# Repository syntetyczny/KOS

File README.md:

KOS
===

Another RepRap controller based on teensylu/printrboard and more. 

Project and all files attached are licensed by Creative Commons license CC BY-NC-ND 3.0 . If you want to comercially use project contact the author:
Paweł Janusz Dobrowolski
email: pawel.j.dobrowolski@gmail.com
company email: pjd@pjd-automatyka.pl

legal links:
http://creativecommons.org/licenses/by-nc-nd/3.0/
http://creativecommons.org/licenses/by-nc-nd/3.0/pl/legalcode
http://creativecommons.org/licenses/by-nc-nd/3.0/pl/

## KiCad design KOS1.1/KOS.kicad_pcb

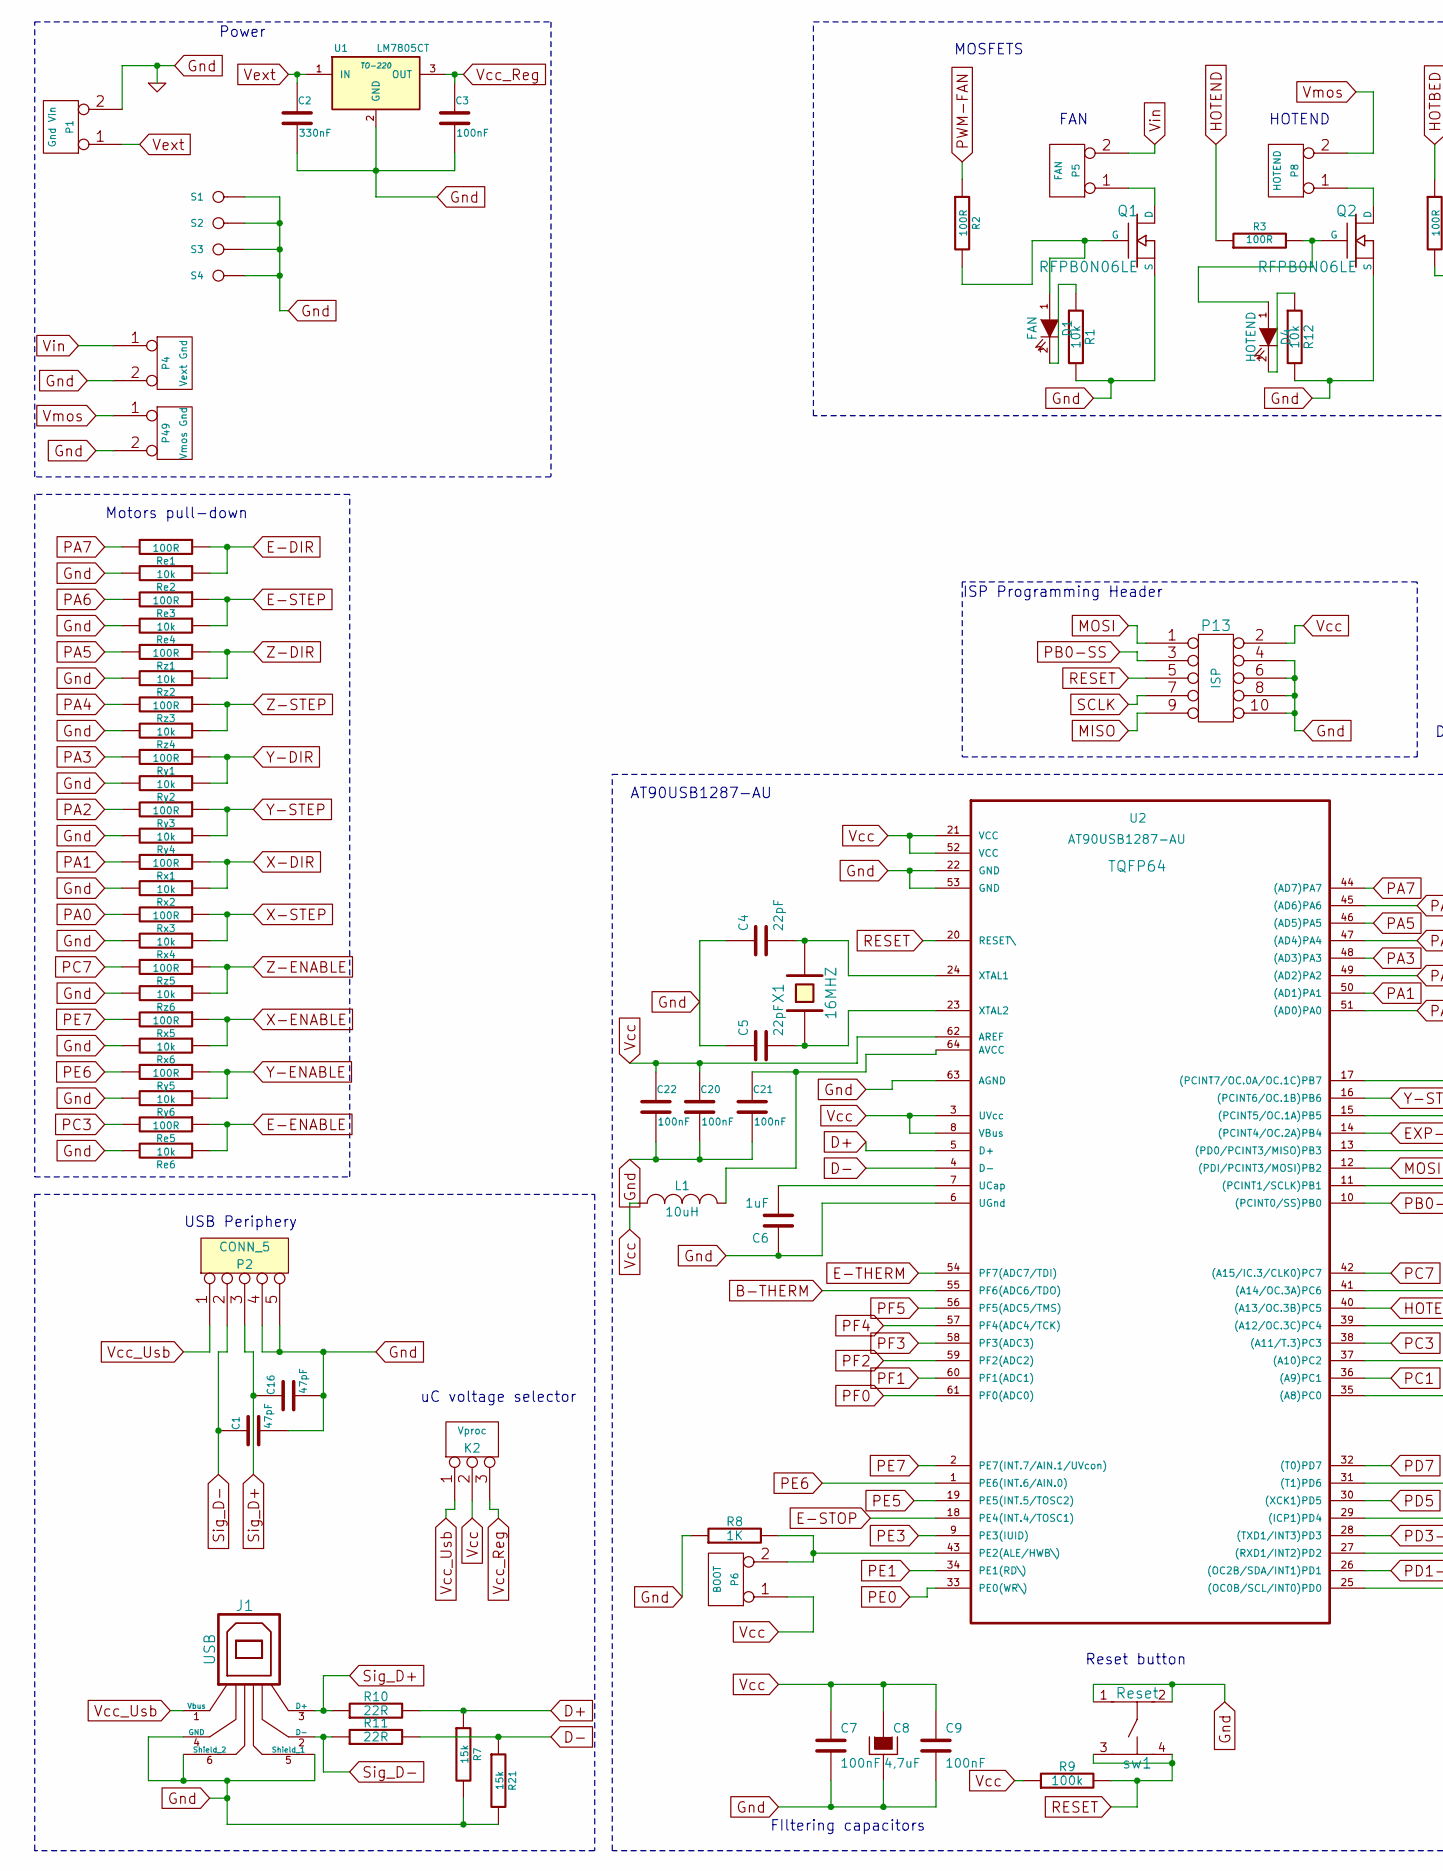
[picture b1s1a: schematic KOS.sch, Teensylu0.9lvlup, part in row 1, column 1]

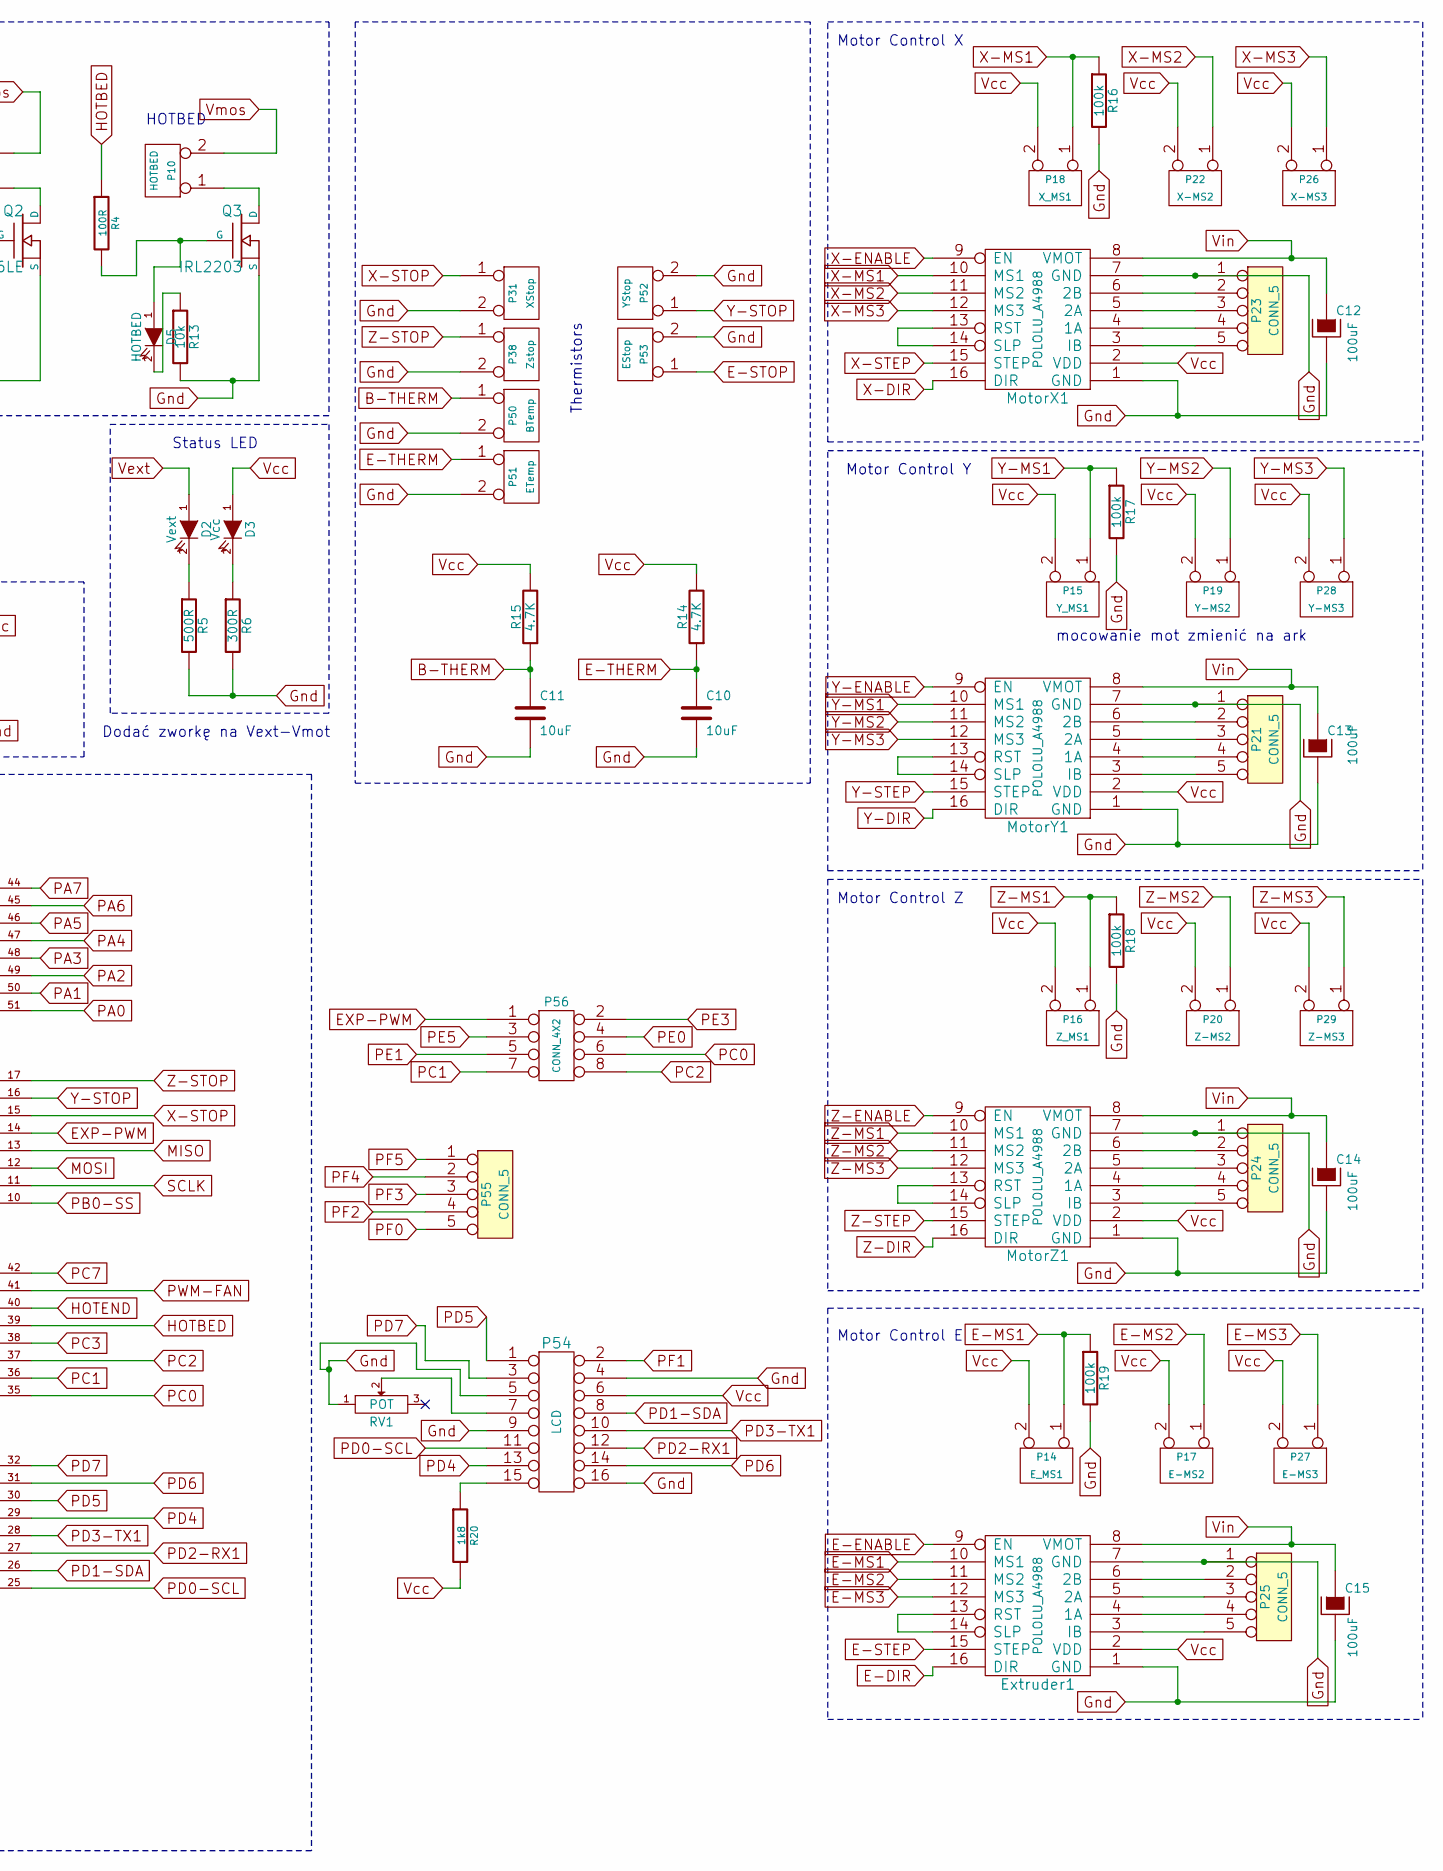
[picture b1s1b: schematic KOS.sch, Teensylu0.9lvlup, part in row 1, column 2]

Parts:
C1, C16: 47pF
C2: 330nF
C3, C7, C9, C20, C21, C22: 100nF
C4, C5: 22pF
C6: 1uF
C8: 4,7uF
C10, C11: 10uF
C12, C13, C14, C15: 100uF
D1: FAN
D2: Vext
D3: Vcc
D4: HOTEND
D5: HOTBED
Extruder1: POLOLU_A4988
J1: USB
K2: Vproc
L1: 10uH
MotorX1: POLOLU_A4988
MotorY1: POLOLU_A4988
MotorZ1: POLOLU_A4988
P1: Gnd Vin
P2, P21, P23, P24, P25, P55: CONN_5
P4: Vext Gnd
P5: FAN
P6: BOOT
P8: HOTEND
P10: HOTBED
P13: ISP
P14: E_MS1
P15: Y_MS1
P16: Z_MS1
P17: E-MS2
P18: X_MS1
P19: Y-MS2
P20: Z-MS2
P22: X-MS2
P26: X-MS3
P27: E-MS3
P28: Y-MS3
P29: Z-MS3
P31: XStop
P38: Zstop
P49: Vmos Gnd
P50: BTemp
P51: ETemp
P52: YStop
P53: EStop
P54: LCD
P56: CONN_4X2
Q1, Q2: RFPB0N06LE
Q3: IRL2203
R1, R12, R13: 10k
R2, R3, R4: 100R
R5: 500R
R6: 300R
R7, R21: 15k
R8: 1K
R9, R16, R17, R18, R19: 100k
R10, R11: 22R
R14, R15: 4.7K
R20: 1k8
RV1: POT
Re1, Re3, Re5: 100R
Re2, Re4, Re6: 10k
Rx1, Rx3, Rx5: 100R
Rx2, Rx4, Rx6: 10k
Ry1, Ry3, Ry5: 100R
Ry2, Ry4, Ry6: 10k
Rz1, Rz3, Rz5: 100R
Rz2, Rz4, Rz6: 10k
S1, S2, S3, S4: S
U1: LM7805CT; TO-220
U2: AT90USB1287-AU
X1: 16MHZ
sw1: Reset

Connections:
B-THERM: C11.1, P50.1, R15.1, U2.55 (PF6(ADC6/TDO))
D+: R7.1, R10.2, U2.5 (D+)
D-: R11.2, R21.1, U2.4 (D-)
E-DIR: Extruder1.16 (DIR), Re1.1, Re2.1
E-ENABLE: Extruder1.9 (EN), Re5.1, Re6.1
E-MS1: Extruder1.10 (MS1), P14.1, R19.1
E-MS2: Extruder1.11 (MS2), P17.1
E-MS3: Extruder1.12 (MS3), P27.1
E-STEP: Extruder1.15 (STEP), Re3.1, Re4.1
E-STOP: P53.1, U2.18 (PE4(INT.4/TOSC1))
E-THERM: C10.1, P51.1, R14.1, U2.54 (PF7(ADC7/TDI))
EXP-PWM: P56.1, U2.14 ((PCINT4/OC.2A)PB4)
Gnd: C1.2, C2.2, C3.2, C4.1, C5.1, C6.1, C7.2, C8.2, C9.2, C10.2, C11.2, C12.2, C13.2, C14.2, C15.2, C16.2, C20.2, C21.2, C22.2, Extruder1.1 (GND), Extruder1.7 (GND), J1.4 (GND), J1.5 (Shield_1), J1.6 (Shield_2), MotorX1.1 (GND), MotorX1.7 (GND), MotorY1.1 (GND), MotorY1.7 (GND), MotorZ1.1 (GND), MotorZ1.7 (GND), P1.2 (PM), P2.4, P2.5, P4.2 (PM), P13.4, P13.6, P13.8, P13.10, P21.1, P23.1, P24.1, P25.1, P31.2 (PM), P38.2 (PM), P49.2 (PM), P50.2 (PM), P51.2 (PM), P52.2 (PM), P53.2 (PM), P54.4, P54.5, P54.9, P54.16, Q1.S, Q2.S, Q3.S, R1.2, R5.2, R6.2, R7.2, R8.1, R12.2, R13.2, R16.2, R17.2, R18.2, R19.2, R21.2, RV1.1, Re2.2, Re4.2, Re6.2, Rx2.2, Rx4.2, Rx6.2, Ry2.2, Ry4.2, Ry6.2, Rz2.2, Rz4.2, Rz6.2, S1.1, S2.1, S3.1, S4.1, U1.2 (GND), U2.6 (UGnd), U2.22 (GND), U2.53 (GND), U2.63 (AGND), sw1.1, sw1.2
HOTBED: R4.1, U2.39 ((A12/OC.3C)PC4)
HOTEND: R3.1, U2.40 ((A13/OC.3B)PC5)
MISO: P13.9, U2.13 ((PD0/PCINT3/MISO)PB3)
MOSI: P13.1, U2.12 ((PDI/PCINT3/MOSI)PB2)
unnamed: Extruder1.13 (RST), Extruder1.14 (SLP)
unnamed: MotorY1.13 (RST), MotorY1.14 (SLP)
unnamed: MotorZ1.13 (RST), MotorZ1.14 (SLP)
unnamed: D5.2 (K), R13.1
unnamed: D5.1 (A), Q3.G, R4.2
unnamed: D4.2 (K), R12.1
unnamed: D1.2 (K), R1.1
unnamed: D3.2 (K), R6.1
unnamed: MotorX1.13 (RST), MotorX1.14 (SLP)
unnamed: C21.1, L1.2, U2.64 (AVCC)
unnamed: D2.2 (K), R5.1
unnamed: P8.1, Q2.D
unnamed: P5.1, Q1.D
unnamed: P10.1, Q3.D
unnamed: C6.2, U2.7 (UCap)
unnamed: P6.2 (PM), R8.2, U2.43 (PE2(ALE/HWB\))
unnamed: P54.15, R20.1
unnamed: P54.7, RV1.2
unnamed: Extruder1.6 (2B), P25.2
unnamed: MotorZ1.3 (IB), P24.5
unnamed: MotorZ1.4 (1A), P24.4
unnamed: MotorZ1.5 (2A), P24.3
unnamed: MotorZ1.6 (2B), P24.2
unnamed: MotorY1.3 (IB), P21.5
unnamed: MotorY1.4 (1A), P21.4
unnamed: MotorY1.5 (2A), P21.3
unnamed: MotorY1.6 (2B), P21.2
unnamed: MotorX1.3 (IB), P23.5
unnamed: MotorX1.4 (1A), P23.4
unnamed: MotorX1.5 (2A), P23.3
unnamed: MotorX1.6 (2B), P23.2
unnamed: Extruder1.3 (IB), P25.5
unnamed: Extruder1.4 (1A), P25.4
unnamed: Extruder1.5 (2A), P25.3
unnamed: D4.1 (A), Q2.G, R3.2
unnamed: D1.1 (A), Q1.G, R2.2
unnamed: C5.2, U2.23 (XTAL2), X1.1
unnamed: C4.2, U2.24 (XTAL1), X1.2
PA0: Rx3.2, U2.51 ((AD0)PA0)
PA1: Rx1.2, U2.50 ((AD1)PA1)
PA2: Ry3.2, U2.49 ((AD2)PA2)
PA3: Ry1.2, U2.48 ((AD3)PA3)
PA4: Rz3.2, U2.47 ((AD4)PA4)
PA5: Rz1.2, U2.46 ((AD5)PA5)
PA6: Re3.2, U2.45 ((AD6)PA6)
PA7: Re1.2, U2.44 ((AD7)PA7)
PB0-SS: P13.3, U2.10 ((PCINT0/SS)PB0)
PC0: P56.6, U2.35 ((A8)PC0)
PC1: P56.7, U2.36 ((A9)PC1)
PC2: P56.8, U2.37 ((A10)PC2)
PC3: Re5.2, U2.38 ((A11/T.3)PC3)
PC7: Rz5.2, U2.42 ((A15/IC.3/CLK0)PC7)
PD0-SCL: P54.11, U2.25 ((OC0B/SCL/INT0)PD0)
PD1-SDA: P54.8, U2.26 ((OC2B/SDA/INT1)PD1)
PD2-RX1: P54.12, U2.27 ((RXD1/INT2)PD2)
PD3-TX1: P54.10, U2.28 ((TXD1/INT3)PD3)
PD4: P54.13, U2.29 ((ICP1)PD4)
PD5: P54.1, U2.30 ((XCK1)PD5)
PD6: P54.14, U2.31 ((T1)PD6)
PD7: P54.3, U2.32 ((T0)PD7)
PE0: P56.4, U2.33 (PE0(WR\))
PE1: P56.5, U2.34 (PE1(RD\))
PE3: P56.2, U2.9 (PE3(IUID))
PE5: P56.3, U2.19 (PE5(INT.5/TOSC2))
PE6: Ry5.2, U2.1 (PE6(INT.6/AIN.0))
PE7: Rx5.2, U2.2 (PE7(INT.7/AIN.1/UVcon))
PF0: P55.5, U2.61 (PF0(ADC0))
PF1: P54.2, U2.60 (PF1(ADC1))
PF2: P55.4, U2.59 (PF2(ADC2))
PF3: P55.3, U2.58 (PF3(ADC3))
PF4: P55.2, U2.57 (PF4(ADC4/TCK))
PF5: P55.1, U2.56 (PF5(ADC5/TMS))
PWM-FAN: R2.1, U2.41 ((A14/OC.3A)PC6)
RESET: P13.5, R9.2, U2.20 (RESET\), sw1.3, sw1.4
SCLK: P13.7, U2.11 ((PCINT1/SCLK)PB1)
Sig_D+: C16.1, J1.3 (D+), P2.3, R10.1
Sig_D-: C1.1, J1.2 (D-), P2.2, R11.1
Vcc: C7.1, C8.1, C9.1, C20.1, C22.1, D3.1 (A), Extruder1.2 (VDD), K2.2 (PM), L1.1, MotorX1.2 (VDD), MotorY1.2 (VDD), MotorZ1.2 (VDD), P6.1, P13.2, P14.2 (PM), P15.2 (PM), P16.2 (PM), P17.2 (PM), P18.2 (PM), P19.2 (PM), P20.2 (PM), P22.2 (PM), P26.2 (PM), P27.2 (PM), P28.2 (PM), P29.2 (PM), P54.6, R9.1, R14.2, R15.2, R20.2, U2.3 (UVcc), U2.8 (VBus), U2.21 (VCC), U2.52 (VCC), U2.62 (AREF)
Vcc_Reg: C3.1, K2.3, U1.3 (OUT)
Vcc_Usb: J1.1 (Vbus), K2.1, P2.1
Vext: C2.1, D2.1 (A), P1.1, U1.1 (IN)
Vin: C12.1, C13.1, C14.1, C15.1, Extruder1.8 (VMOT), MotorX1.8 (VMOT), MotorY1.8 (VMOT), MotorZ1.8 (VMOT), P4.1, P5.2 (PM)
Vmos: P8.2 (PM), P10.2 (PM), P49.1
X-DIR: MotorX1.16 (DIR), Rx1.1, Rx2.1
X-ENABLE: MotorX1.9 (EN), Rx5.1, Rx6.1
X-MS1: MotorX1.10 (MS1), P18.1, R16.1
X-MS2: MotorX1.11 (MS2), P22.1
X-MS3: MotorX1.12 (MS3), P26.1
X-STEP: MotorX1.15 (STEP), Rx3.1, Rx4.1
X-STOP: P31.1, U2.15 ((PCINT5/OC.1A)PB5)
Y-DIR: MotorY1.16 (DIR), Ry1.1, Ry2.1
Y-ENABLE: MotorY1.9 (EN), Ry5.1, Ry6.1
Y-MS1: MotorY1.10 (MS1), P15.1, R17.1
Y-MS2: MotorY1.11 (MS2), P19.1
Y-MS3: MotorY1.12 (MS3), P28.1
Y-STEP: MotorY1.15 (STEP), Ry3.1, Ry4.1
Y-STOP: P52.1, U2.16 ((PCINT6/OC.1B)PB6)
Z-DIR: MotorZ1.16 (DIR), Rz1.1, Rz2.1
Z-ENABLE: MotorZ1.9 (EN), Rz5.1, Rz6.1
Z-MS1: MotorZ1.10 (MS1), P16.1, R18.1
Z-MS2: MotorZ1.11 (MS2), P20.1
Z-MS3: MotorZ1.12 (MS3), P29.1
Z-STEP: MotorZ1.15 (STEP), Rz3.1, Rz4.1
Z-STOP: P38.1, U2.17 ((PCINT7/OC.0A/OC.1C)PB7)

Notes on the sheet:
Status LED
ISP Programming Header
MOSFETS
FIltering capacitors
Reset button
Motor Control Y
Motor Control Z
Motor Control E
Motor Control X
Thermistors
AT90USB1287-AU
FAN
HOTEND
HOTBED
USB Periphery
uC voltage selector
Motors pull-down
Power
mocowanie mot zmienić na ark
Dodać zworkę na Vext-Vmot

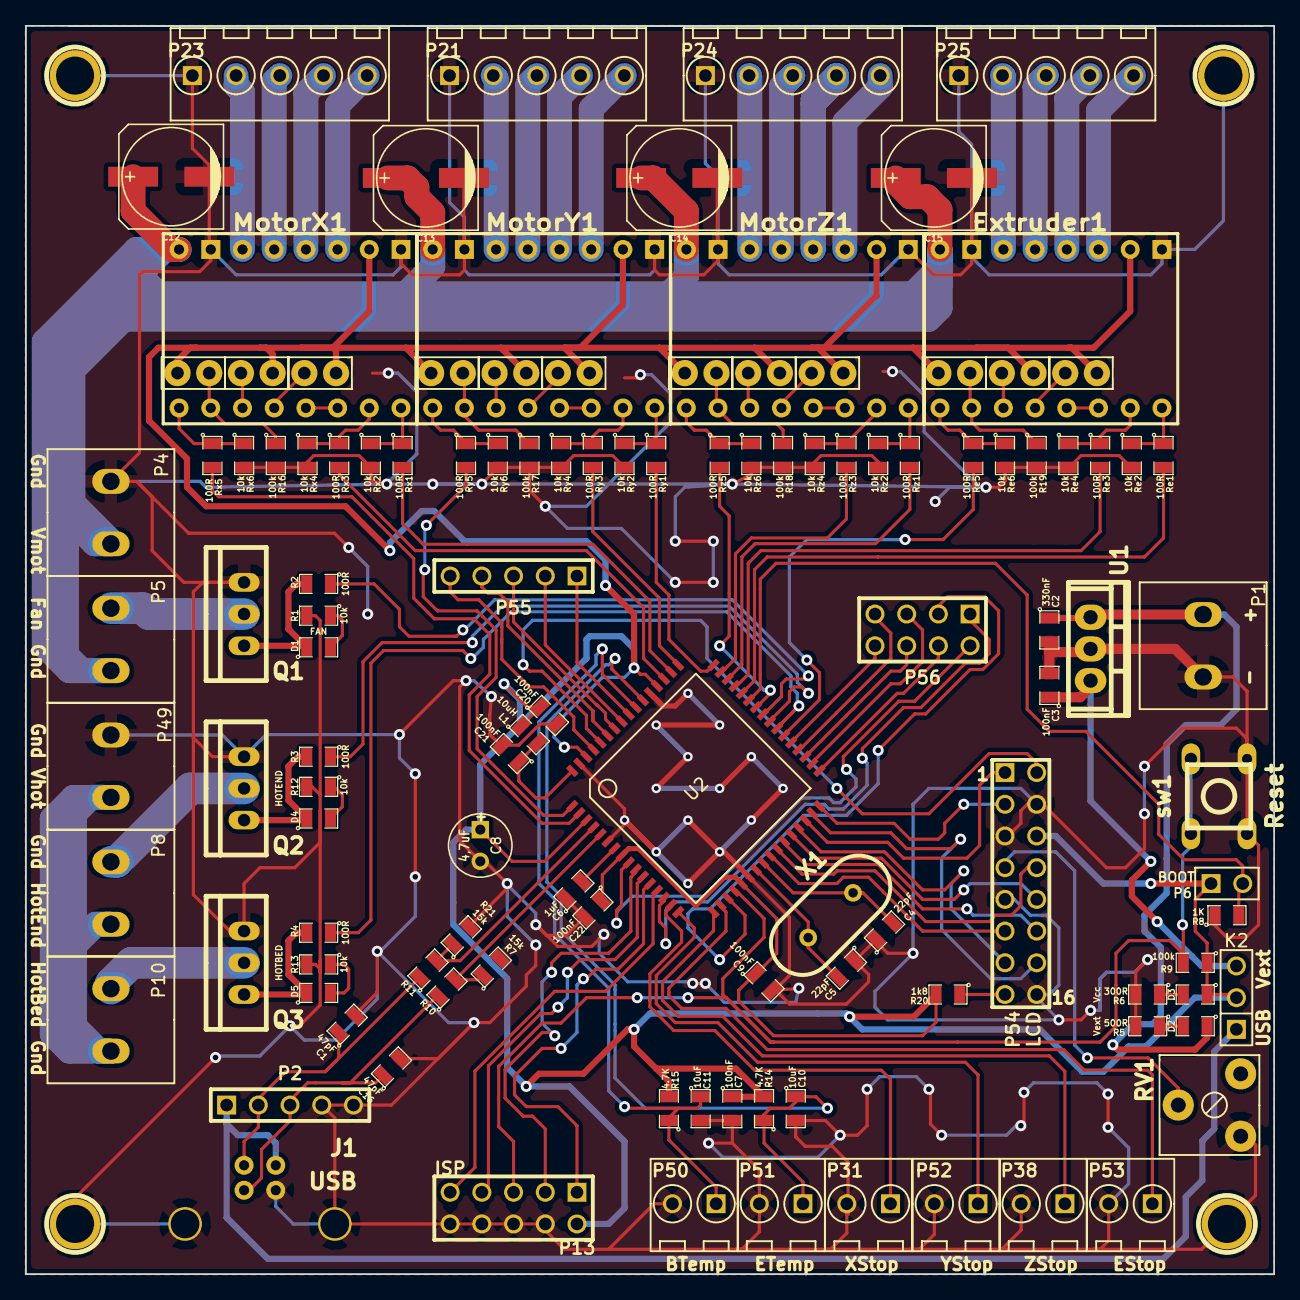
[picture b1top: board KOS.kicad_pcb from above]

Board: 2 copper layers, 100.0 x 100.0 mm, 122 parts (0 on the bottom side), 121 nets.

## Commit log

2014-06-26 New version of KOS added with manuals
2014-06-26 Remove gerb directory
2014-06-26 Remove multiple files
2014-06-26 Remove comment files
2014-06-26 Changed pdf manuals
2014-06-26 Added README
